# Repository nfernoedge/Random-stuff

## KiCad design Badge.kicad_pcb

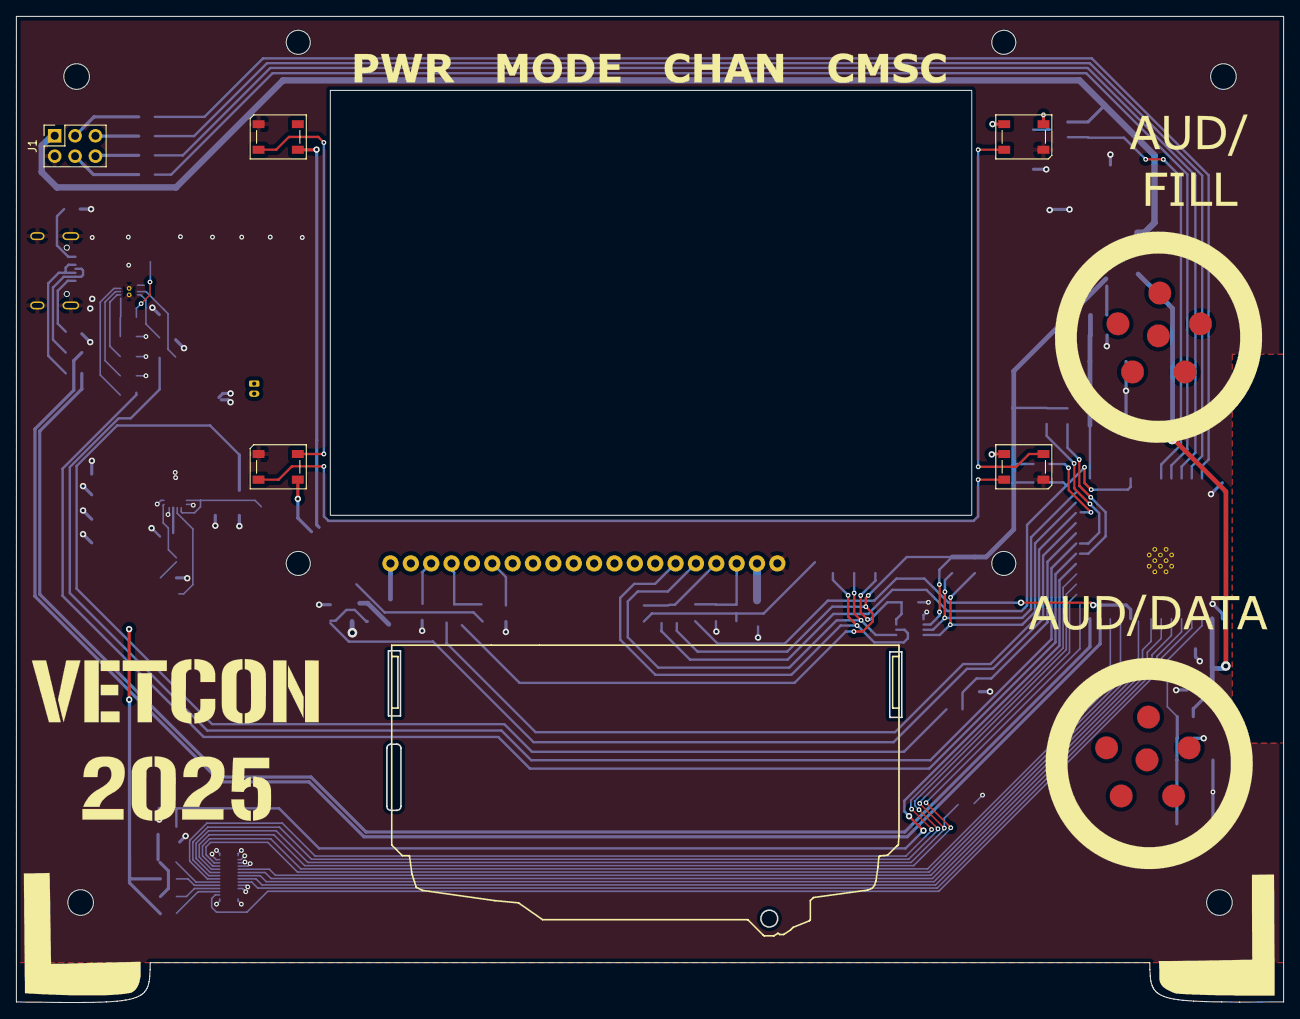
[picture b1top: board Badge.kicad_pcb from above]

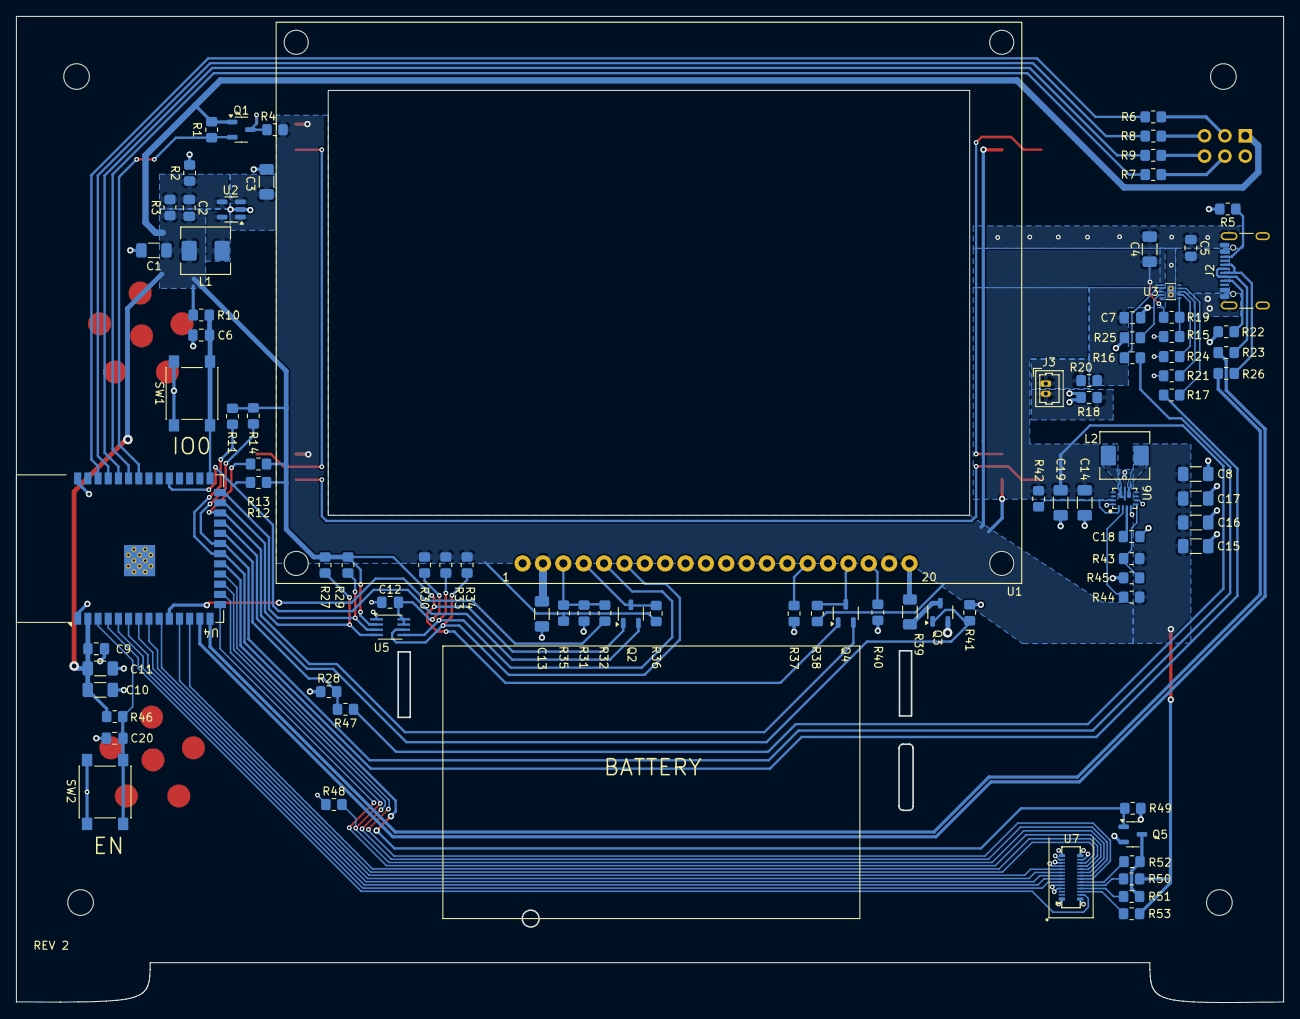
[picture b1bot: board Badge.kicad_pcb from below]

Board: 2 copper layers, 158.0 x 122.9 mm, 96 parts (90 on the bottom side), 80 nets.

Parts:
C1, C8, C10, C11, C13, C14, C19: 10uF; C_1206_3216Metric_Pad1.33x1.80mm_HandSolder
C2: 22pF; C_0805_2012Metric_Pad1.18x1.45mm_HandSolder
C3: 10uf; C_1206_3216Metric_Pad1.33x1.80mm_HandSolder
C4: 10u; C_1206_3216Metric_Pad1.33x1.80mm_HandSolder
C5, C7: 1u; C_0805_2012Metric_Pad1.18x1.45mm_HandSolder
C6, C9, C12, C20: .1u; C_0805_2012Metric_Pad1.18x1.45mm_HandSolder
C15, C16, C17: 22uF; C_1206_3216Metric_Pad1.33x1.80mm_HandSolder
C18: .1uF; C_0805_2012Metric_Pad1.18x1.45mm_HandSolder
D1, D2, D3, D4: Inolux_IN-PI554FCH; LED_Inolux_IN-PI554FCH_PLCC4_5.0x5.0mm_P3.2mm
J1: Conn_02x03_Odd_Even; PinSocket_2x03_P2.54mm_Vertical
J2: USB_C_Receptacle; USB_C_Receptacle_GCT_USB4105-xx-A_16P_TopMnt_Horizontal
J3: B2B-XH-A; Molex_PicoBlade_53047-0210_1x02_P1.25mm_Vertical
L1, L2: 2.2uH; L_Chilisin_BMRA00050530
Q1, Q2, Q3, Q4, Q5: Q_NMOS_GSD; SOT-23-3
R1, R4, R10, R11, R12, R13, R14, R15, R19, R25, R27, R29, R33, R34, R36, R37, R38, R41, R42, R44, R46, R48, R49: 10k; R_0805_2012Metric_Pad1.20x1.40mm_HandSolder
R2: 100k; R_0805_2012Metric_Pad1.20x1.40mm_HandSolder
R3: 430k; R_0805_2012Metric_Pad1.20x1.40mm_HandSolder
R5, R22: 5.1k; R_0805_2012Metric_Pad1.20x1.40mm_HandSolder
R6, R7, R8, R9: 100; R_0805_2012Metric_Pad1.20x1.40mm_HandSolder
R16, R17, R18, R20, R43: 0; R_0805_2012Metric_Pad1.20x1.40mm_HandSolder
R21: 1k; R_0805_2012Metric_Pad1.20x1.40mm_HandSolder
R23, R26: 15; R_0805_2012Metric_Pad1.20x1.40mm_HandSolder
R24: 5k; R_0805_2012Metric_Pad1.20x1.40mm_HandSolder
R28: 6.8k; R_0805_2012Metric_Pad1.20x1.40mm_HandSolder
R30: 200k; R_0805_2012Metric_Pad1.20x1.40mm_HandSolder
R31, R32, R35, R40, R50, R51, R52, R53: 200; R_0805_2012Metric_Pad1.20x1.40mm_HandSolder
R39: 3; R_1206_3216Metric_Pad1.30x1.75mm_HandSolder
R45: DNP; R_0805_2012Metric_Pad1.20x1.40mm_HandSolder
R47: 3.9k; R_0805_2012Metric_Pad1.20x1.40mm_HandSolder
SW1, SW2: SW_Push; SW_SPST_PTS645
U1: LCD12864; TZT_LCD12864_RearMount
U2: AP3428A; TSOT-23-5
U3: BQ25185; WSON-10
U4: ESP32-S3-WROOM-1
U5: PCA9306; SSOP-8_2.95x2.8mm_P0.65mm
U6: TPS63070; VQFN-TPS63070
U7: BBQ10KBD; BM14B(0.8)-24DS-0.4V(53)

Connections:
+3V3: C1.1, C2.1, C9.1, C10.1, C11.1, J1.1, L1.2, Q1.1 (G), Q2.1 (G), Q4.1 (G), R1.1, R3.1, R10.1, R11.1, R12.2, R13.2, R14.1, R27.2, R29.2, R46.1, U4.2 (3V3), U5.2 (VREF1)
+5V: C3.1, C8.1, C13.1, C15.1, C16.1, C17.1, D1.3 (VDD), D2.3 (VDD), D3.3 (VDD), D4.3 (VDD), R4.1, R30.2, R33.2, R34.2, R35.2, R36.2, R38.2, R43.1, R44.2, R50.2, R53.2, U1.2 (VDD), U1.19 (A), U2.1 (VIN), U2.3 (EN), U6.7 (VOUT), U6.8
+BATT: C7.1, R20.2, U3.2 (BAT)
/BAT_STAT1: R11.2, R17.2, U4.20 (IO12)
/BAT_STAT2: R14.2, R16.2, U4.21 (IO13)
/CON_BAT+: J3.1, R20.1
/CON_BAT-: J3.2, R18.1
/EN: C20.1, R46.2, SW2.2, U4.3 (EN)
/IO0: C6.1, R10.2, SW1.2, U4.27 (IO0)
/KBD_BL_PWM: Q5.1 (G), R49.2, U4.19 (IO11)
/KBD_COL1: U4.6 (IO6), U7.7 (COL1)
/KBD_COL2: U4.8 (IO15), U7.9 (COL2)
/KBD_COL3: U4.9 (IO16), U7.10 (COL3)
/KBD_COL4: U4.11 (IO18), U7.17 (COL4)
/KBD_COL5: U4.15 (IO3), U7.19 (COL5)
/KBD_ROW1: U4.5 (IO5), U7.6 (ROW1)
/KBD_ROW2: U4.7 (IO7), U7.8 (ROW2)
/KBD_ROW3: U4.12 (IO8), U7.18 (ROW3)
/KBD_ROW4: R48.2, U4.16 (IO46), U7.20 (ROW4)
/KBD_ROW5: U4.17 (IO9), U7.21 (ROW5)
/KBD_ROW6: U4.18 (IO10), U7.22 (ROW6)
/KBD_ROW7: U4.4 (IO4), U7.27 (ROW7)
/LCD_BL_PWM: Q3.1 (G), R41.2, U4.23 (IO21)
/LCD_CLK: R29.1, U4.26 (IO45), U5.3 (SCL1)
/LCD_CONT: R32.1, U4.10 (IO17)
/LCD_CS: Q2.2 (S), R12.1, U4.31 (IO38)
/LCD_DATA: R27.1, U4.25 (IO48), U5.4 (SDA1)
/LCD_RST: Q4.2 (S), R13.1, U4.24 (IO47)
/LED_DATA: Q1.2 (S), R1.2, U4.34 (IO41)
/SAO_GPIO1: R8.1, U4.37 (TXD0)
/SAO_GPIO2: R9.2, U4.36 (RXD0)
/SAO_SCL: R7.2, U4.35 (IO42)
/SAO_SDA: R6.1, U4.38 (IO2)
/USB_DN: R23.2, U4.13 (USB_D-)
/USB_DP: R26.1, U4.14 (USB_D+)
GND: C1.2, C3.2, C4.2, C5.2, C6.2, C7.2, C8.2, C9.2, C10.2, C11.2, C12.2, C13.2, C14.2, C15.2, C16.2, C17.2, C18.2, C19.2, C20.2, D1.1 (VSS), D2.1 (VSS), D3.1 (VSS), D4.1 (VSS), J1.2, J2.A1 (GND), J2.A12 (GND), J2.B1 (GND), J2.B12 (GND), J2.S1 (SHIELD), Q3.2 (S), Q5.2 (S), R2.2, R5.2, R15.2, R18.2, R21.2, R22.2, R24.2, R25.2, R28.2, R31.1, R37.1, R40.1, R41.1, R45.2, R48.1, R49.1, SW1.1, SW2.1, U1.1 (VSS), U2.2 (GND), U3.5 (GND), U3.11 (GND), U4.1 (GND), U4.40 (GND), U4.41 (GND), U5.1 (GND), U6.4 (GND), U6.6 (FB2), U6.10 (PGND), U6.15 (VSEL), U7.1 (GND), U7.4 (AGND), U7.5 (GND), U7.11 (GND), U7.12 (GND), U7.13 (GND), U7.14 (GND), U7.15 (GND), U7.16 (GND), U7.28 (GND)
unnamed: D1.2 (DIN), D3.4 (DO)
unnamed: D2.2 (DIN), Q1.3 (D), R4.2
unnamed: D2.4 (DO), D4.2 (DIN)
unnamed: D3.2 (DIN), D4.4 (DO)
unnamed: J1.3, R6.2
unnamed: J1.4, R7.1
unnamed: J1.5, R8.2
unnamed: J1.6, R9.1
unnamed: J2.A5 (CC1), R22.1
unnamed: J2.B5 (CC2), R5.1
unnamed: J2.A6 (D+), J2.B6 (D+), R26.2
unnamed: J2.A7 (D-), J2.B7 (D-), R23.1
unnamed: Q2.3 (D), R36.1, U1.4 (RS|CS)
unnamed: Q4.3 (D), R38.1, U1.17 (~RESET)
unnamed: Q3.3 (D), R39.1
unnamed: Q5.3 (D), R51.1, R52.1
unnamed: R34.1, U1.6 (E|CLK), U5.6 (SCL2)
unnamed: R39.2, U1.20 (K)
unnamed: R37.2, U1.15 (PSB)
unnamed: R33.1, U1.5 (R/~W|SID), U5.5 (SDA2)
unnamed: R31.2, R32.2, R35.1, U1.3 (V0)
unnamed: R40.2, U1.18 (VOUT)
unnamed: C2.2, R2.1, R3.2, U2.4 (FB)
unnamed: L1.1, U2.5 (LX)
unnamed: R24.1, U3.7 (ILIM/VSET)
unnamed: R21.1, U3.8 (ISET)
unnamed: R17.1, U3.9 (STAT1)
unnamed: R16.1, U3.3 (STAT2)
unnamed: R15.1, R19.2, U3.6 (TS/MR)
unnamed: R25.1, U3.4 (~CE)
unnamed: R28.1, R47.2, U4.22 (IO14)
unnamed: C12.1, R30.1, U5.7 (VREF2), U5.8 (EN)
unnamed: R42.2, U6.1 (PS/SYNC), U6.14 (EN)
unnamed: R43.2, R45.1, U6.5 (FB)
unnamed: L2.2, U6.11 (L1)
unnamed: L2.1, U6.9 (L2)
unnamed: R44.1, U6.2 (PG)
unnamed: C18.1, U6.3 (VAUX)
unnamed: R53.1, U7.26 (LEDA_1_2)
unnamed: R50.1, U7.24 (LEDA_3_4)
unnamed: R51.2, U7.25 (LEDK_1_4)
unnamed: R52.2, U7.23 (LEDK_2_3)
VBUS: C5.1, J2.A4 (VBUS), J2.A9 (VBUS), J2.B4 (VBUS), J2.B9 (VBUS), U3.10 (IN)
VSYS: C4.1, C14.1, C19.1, R19.1, R42.1, R47.1, U3.1 (SYS), U6.12 (VIN), U6.13
